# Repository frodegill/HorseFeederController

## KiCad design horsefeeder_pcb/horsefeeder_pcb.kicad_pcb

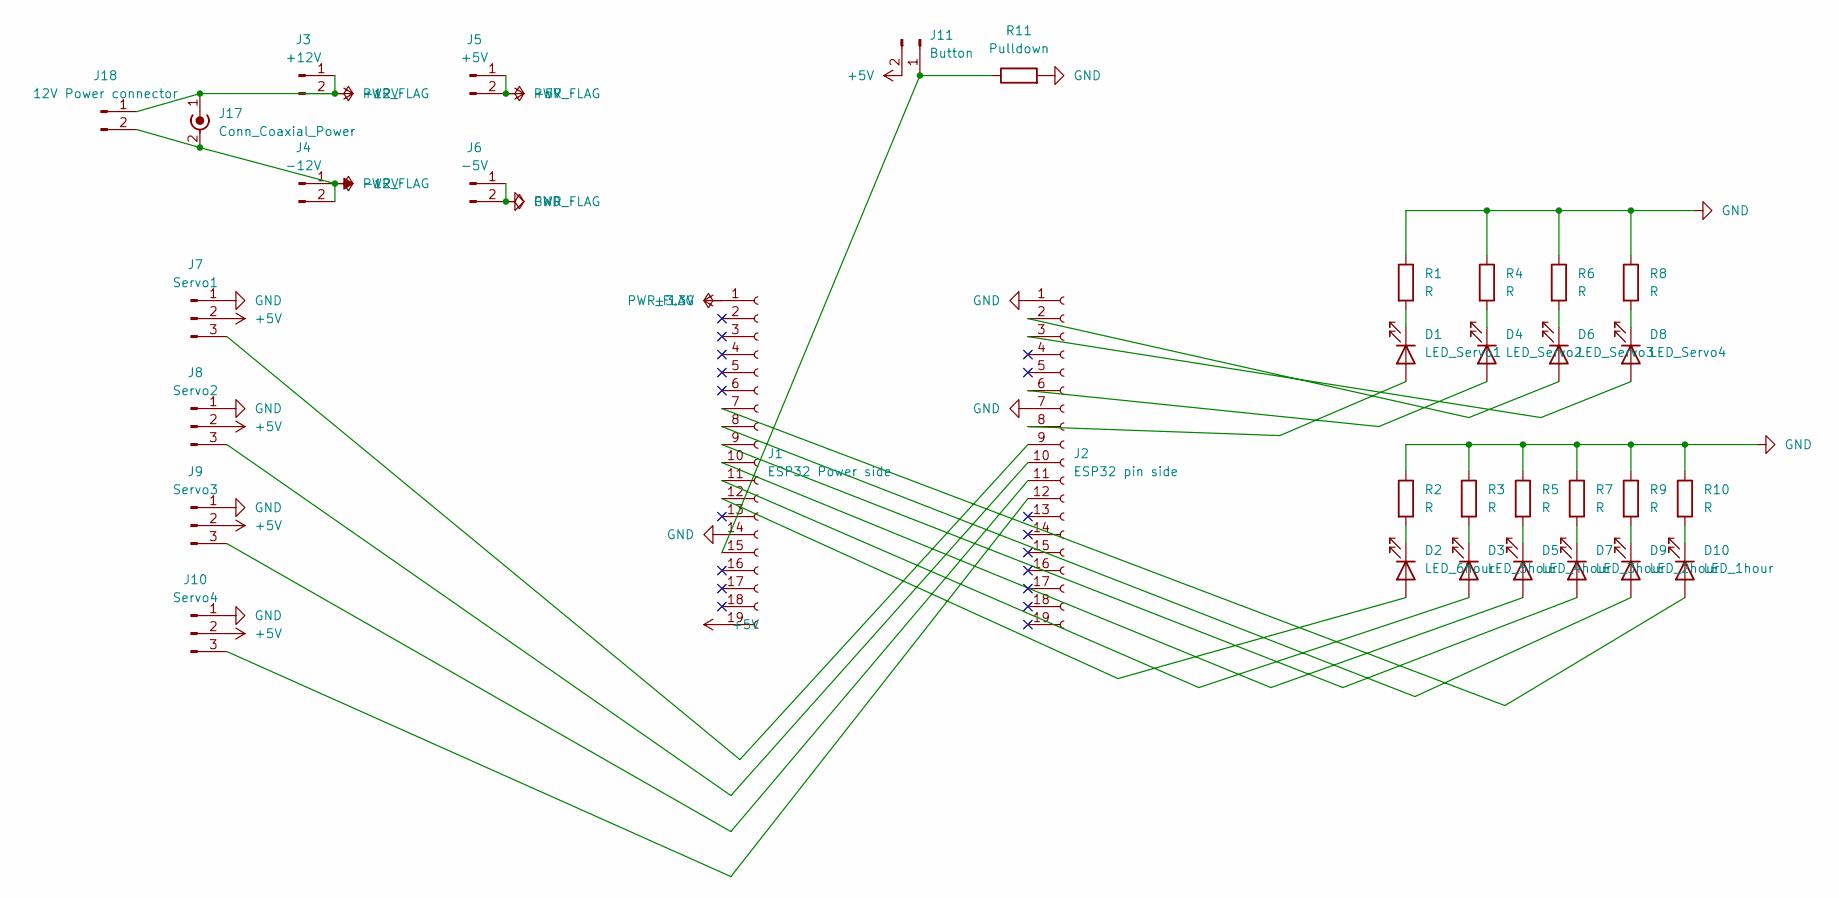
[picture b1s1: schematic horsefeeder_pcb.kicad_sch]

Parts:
D1: LED_Servo1; LED_PLCC_2835_AK
D2: LED_6hour; LED_PLCC_2835_AK
D3: LED_5hour; LED_PLCC_2835_AK
D4: LED_Servo2; LED_PLCC_2835_AK
D5: LED_4hour; LED_PLCC_2835_AK
D6: LED_Servo3; LED_PLCC_2835_AK
D7: LED_3hour; LED_PLCC_2835_AK
D8: LED_Servo4; LED_PLCC_2835_AK
D9: LED_2hour; LED_PLCC_2835_AK
D10: LED_1hour; LED_PLCC_2835_AK
J1: ESP32 Power side; PinHeader_1x19_P2.54mm_Vertical
J2: ESP32 pin side; PinHeader_1x19_P2.54mm_Vertical
J3: +12V; PinHeader_1x02_P2.54mm_Vertical
J4: -12V; PinHeader_1x02_P2.54mm_Vertical
J5: +5V; PinHeader_1x02_P2.54mm_Vertical
J6: -5V; PinHeader_1x02_P2.54mm_Vertical
J7: Servo1; PinHeader_1x03_P2.54mm_Vertical
J8: Servo2; PinHeader_1x03_P2.54mm_Vertical
J9: Servo3; PinHeader_1x03_P2.54mm_Vertical
J10: Servo4; PinHeader_1x03_P2.54mm_Vertical
J11: Button; PinHeader_1x02_P2.54mm_Vertical
J17: Conn_Coaxial_Power; BarrelJack_Wuerth_6941xx301002
J18: 12V Power connector; TerminalBlock_bornier-2_P5.08mm
R1, R2, R3, R4, R5, R6, R7, R8, R9, R10: R; R_1206_3216Metric
R11: Pulldown; R_1206_3216Metric

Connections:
+3.3V: J1.1
+5V: J1.19, J5.1, J5.2, J7.2, J8.2, J9.2, J10.2, J11.2
+12V: J3.1, J3.2, J17.1 (In), J18.1
-12V: J4.1, J4.2, J17.2 (Ext), J18.2
GND: J1.14, J2.1, J2.7, J6.1, J6.2, J7.1, J8.1, J9.1, J10.1, R1.1, R2.1, R3.1, R4.1, R5.1, R6.1, R7.1, R8.1, R9.1, R10.1, R11.2
unnamed: D1.1 (K), R1.2
unnamed: D2.1 (K), R2.2
unnamed: D3.1 (K), R3.2
unnamed: D4.1 (K), R4.2
unnamed: D4.2 (A), J2.6
unnamed: D5.1 (K), R5.2
unnamed: D6.1 (K), R6.2
unnamed: D6.2 (A), J2.2
unnamed: D7.1 (K), R7.2
unnamed: D8.1 (K), R8.2
unnamed: D8.2 (A), J2.3
unnamed: D9.1 (K), R9.2
unnamed: D10.1 (K), R10.2
unnamed: D10.2 (A), J1.7
unnamed: D9.2 (A), J1.8
unnamed: D7.2 (A), J1.9
unnamed: D5.2 (A), J1.10
unnamed: D3.2 (A), J1.11
unnamed: D2.2 (A), J1.12
unnamed: J1.15, J11.1, R11.1
unnamed: D1.2 (A), J2.8
unnamed: J2.9, J7.3
unnamed: J2.10, J8.3
unnamed: J2.11, J9.3
unnamed: J2.12, J10.3

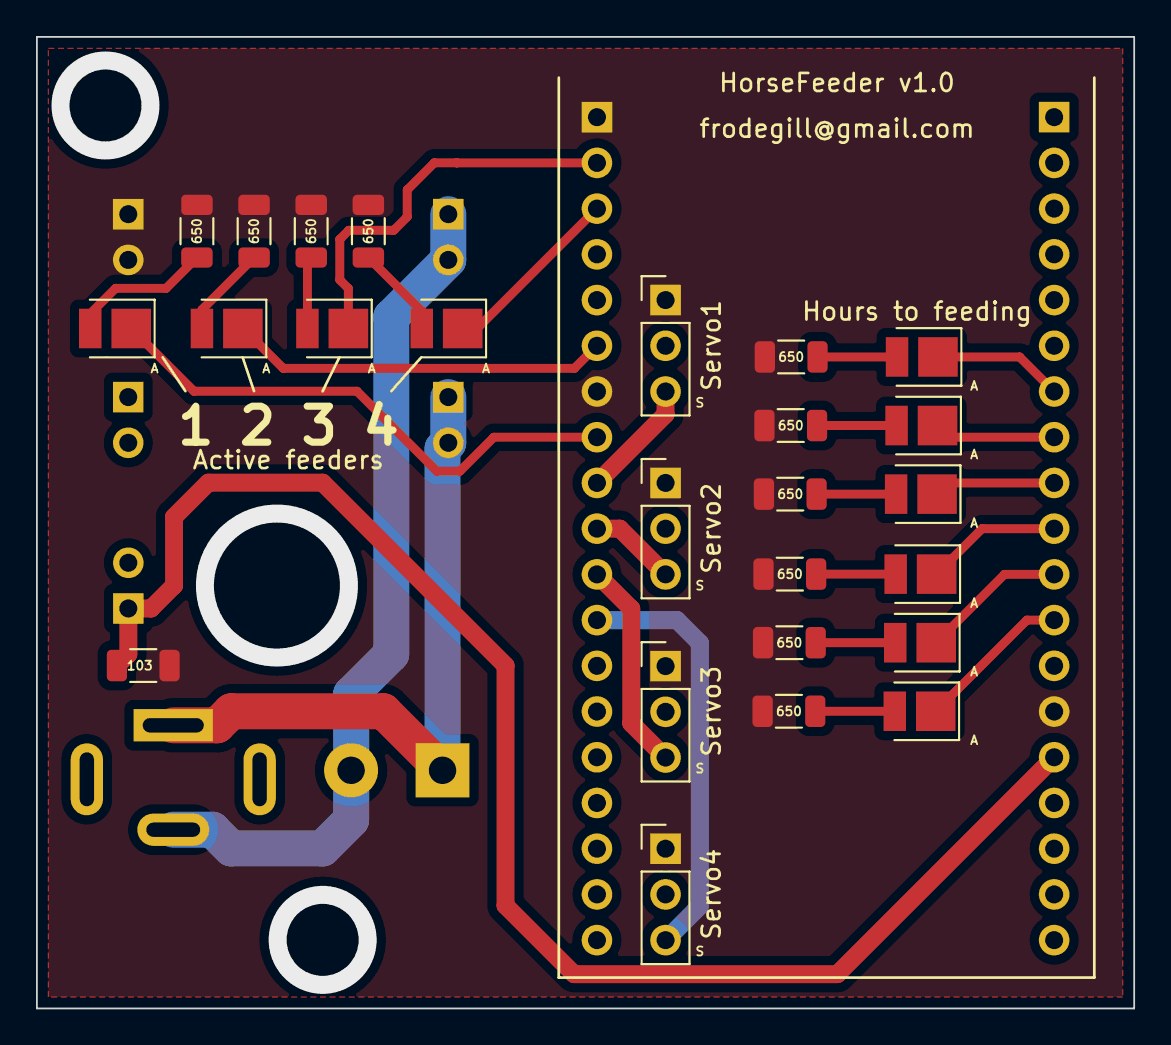
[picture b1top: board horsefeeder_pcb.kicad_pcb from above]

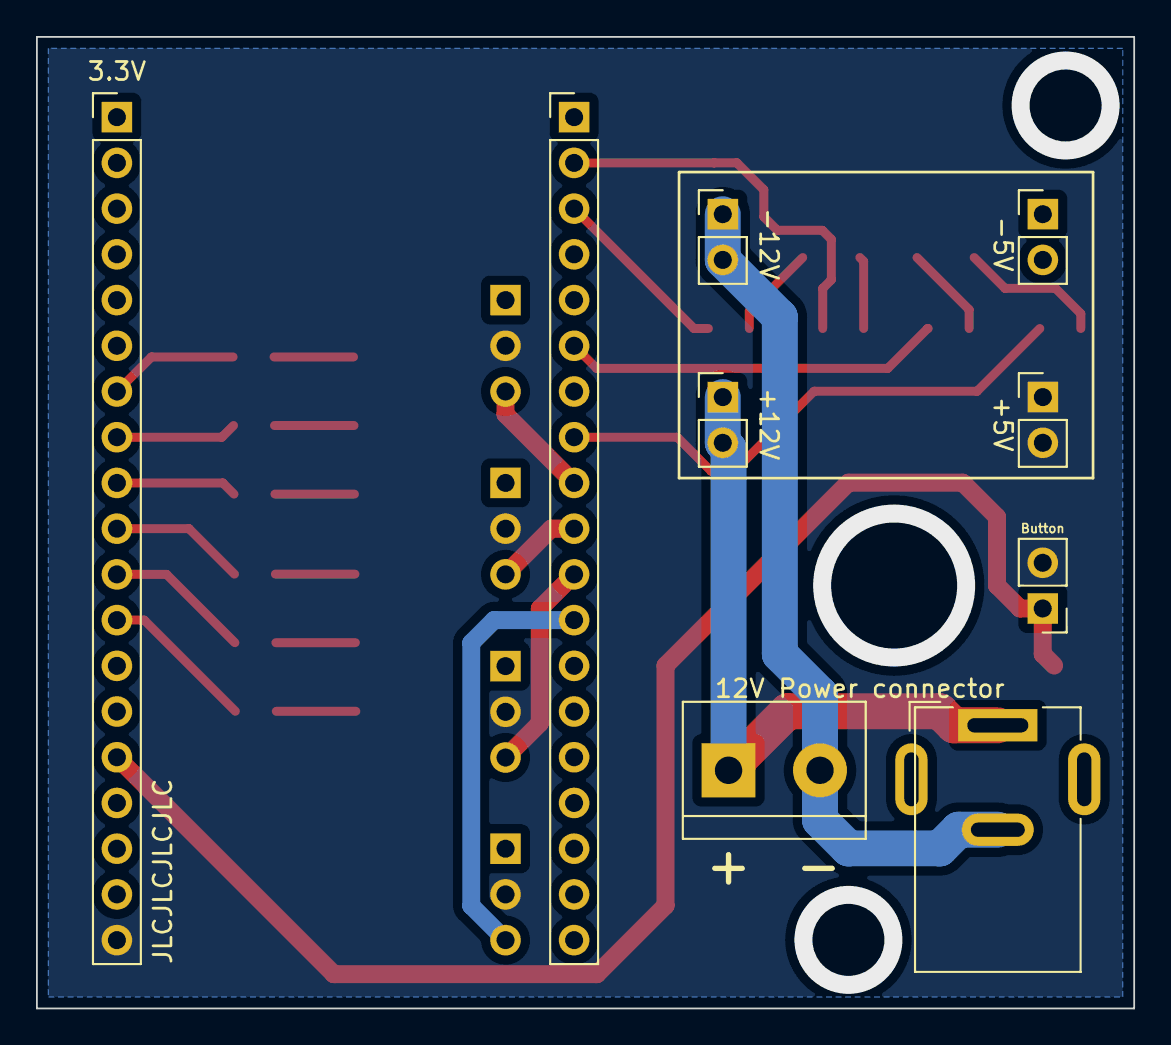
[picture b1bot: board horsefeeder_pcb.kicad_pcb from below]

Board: 2 copper layers, 61.0 x 54.0 mm, 34 parts (9 on the bottom side), 29 nets.

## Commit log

2024-03-05 Added PCB
2024-03-07 Completely untested ESP32 code
2024-03-07 Added support for GPIOViewer
2024-03-29 Fixed ground zone problem
2024-03-29 Minor bugfix after full 24H run
2024-03-31 Added testmode for servos
2024-07-23 Adjustments to match E-flite EFLRS75 servos
